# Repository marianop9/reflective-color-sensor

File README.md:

# Sensor de Colores por Reflexión

Este proyecto consiste en el diseño e implementación de un **sensor de color de bajo costo** capaz de estimar el color de una superficie y representarlo en formato RGB de 24 bits. El sistema utiliza una fotorresistencia (LDR) como transductor principal, compensando sus limitaciones mediante un proceso de caracterización empírica y un circuito de acondicionamiento activo.

## Características Principales
* **Hardware:** Basado en el microcontrolador **RP2040** (Raspberry Pi Pico).
* **Iluminantes:** LEDs RGB direccionables **WS2812**, controlados mediante el hardware PIO del RP2040 para máxima precisión.
* **Acondicionamiento:** Circuito de ganancia programable utilizando el switch bilateral **CD4066**, permitiendo medir un amplio rango de resistencias del LDR (1 k&Omega; a 1 M&Omega;) sin saturación.
* **Software:** Firmware desarrollado en C con **FreeRTOS** y **TinyUSB**. Aplicación de control en Python (CLI) para procesamiento de datos.

## Principio de Funcionamiento

El sensor opera utilizando la **reflexión secuencial**. El proceso se divide en los siguientes pasos:

1. **Aislamiento:** La carcasa diseñada bloquea la luz ambiente para evitar interferencias en la medición.
2. **Iluminación:** El dispositivo enciende secuencialmente los canales Rojo, Verde y Azul de los LEDs.
3. **Detección:** El LDR recibe la luz reflejada por la superficie. Su resistencia cambia según la intensidad recibida, y el circuito de acondicionamiento convierte este cambio en una tensión medible por el ADC.
4. **Procesamiento:** El microcontrolador envía los valores a una PC vía USB (CDC), donde se calcula el color final aplicando los parámetros de calibración.

## Caracterización y Calibración del LDR

Dado que los LDR presentan baja trazabilidad y una respuesta no lineal que varía según la longitud de onda , se implementó un procedimiento de **calibración por mínimos cuadrados**.

### El Modelo
Se modela la conductancia ($G$) del LDR en función de la intensidad de la luz ($c$) mediante la ecuación:
$$G = K_a c^{\gamma}$$
Donde $K_a$ y $\gamma$ son parámetros específicos para cada color y cada componente individual.

### Proceso de Calibración
1. Se realiza un **barrido logarítmico de intensidad** (de 0 a 255) para cada canal (R, G, B) sobre una superficie blanca de referencia.
2. Se recolectan las muestras de tensión y se ajusta automáticamente la ganancia ($R_f$) para mantener la señal en la zona lineal del ADC.
3. Mediante un script de Python, se aplica la técnica de **mínimos cuadrados** sobre los datos para hallar los coeficientes $K_a$ y $\gamma$ para cada color por separado.
4. Estos coeficientes se guardan en un archivo JSON que la aplicación CLI utiliza para convertir las mediciones posteriores en códigos de color precisos.

## Estructura del Repositorio
* `/firmware`: Código fuente en C para el RP2040 (Pico-SDK).
* `/scripts`: Contiene la Aplicación CLI en Python y varios scripts de procesamiento de datos.
* `/hardware`: Modelado de las carcasas del dispositivo para impresión 3D.
* `/circuitos`: Esquemáticos del circuito de acondicionamiento y simulaciones en LTSpice.
* `/docs`: Informes técnicos detallados del proyecto.

## Resultados

Utilizando la siguiente hoja de prueba, se tomaron medidas de las superficies de color utilizando distintas aplicaciones móviles, bajo distintas condiciones de iluminación ambiente, y se compararon con las medidas obtenidas con el dispositivo.

---

- **Autores:** Federico Beck & Mariano Perez 
- **Institución:** Universidad Tecnológica Nacional - Facultad Regional San Francisco.

Entregado como trabajo integrador de las materías Médidas Electrónicas II y Técnicas Digitales III.

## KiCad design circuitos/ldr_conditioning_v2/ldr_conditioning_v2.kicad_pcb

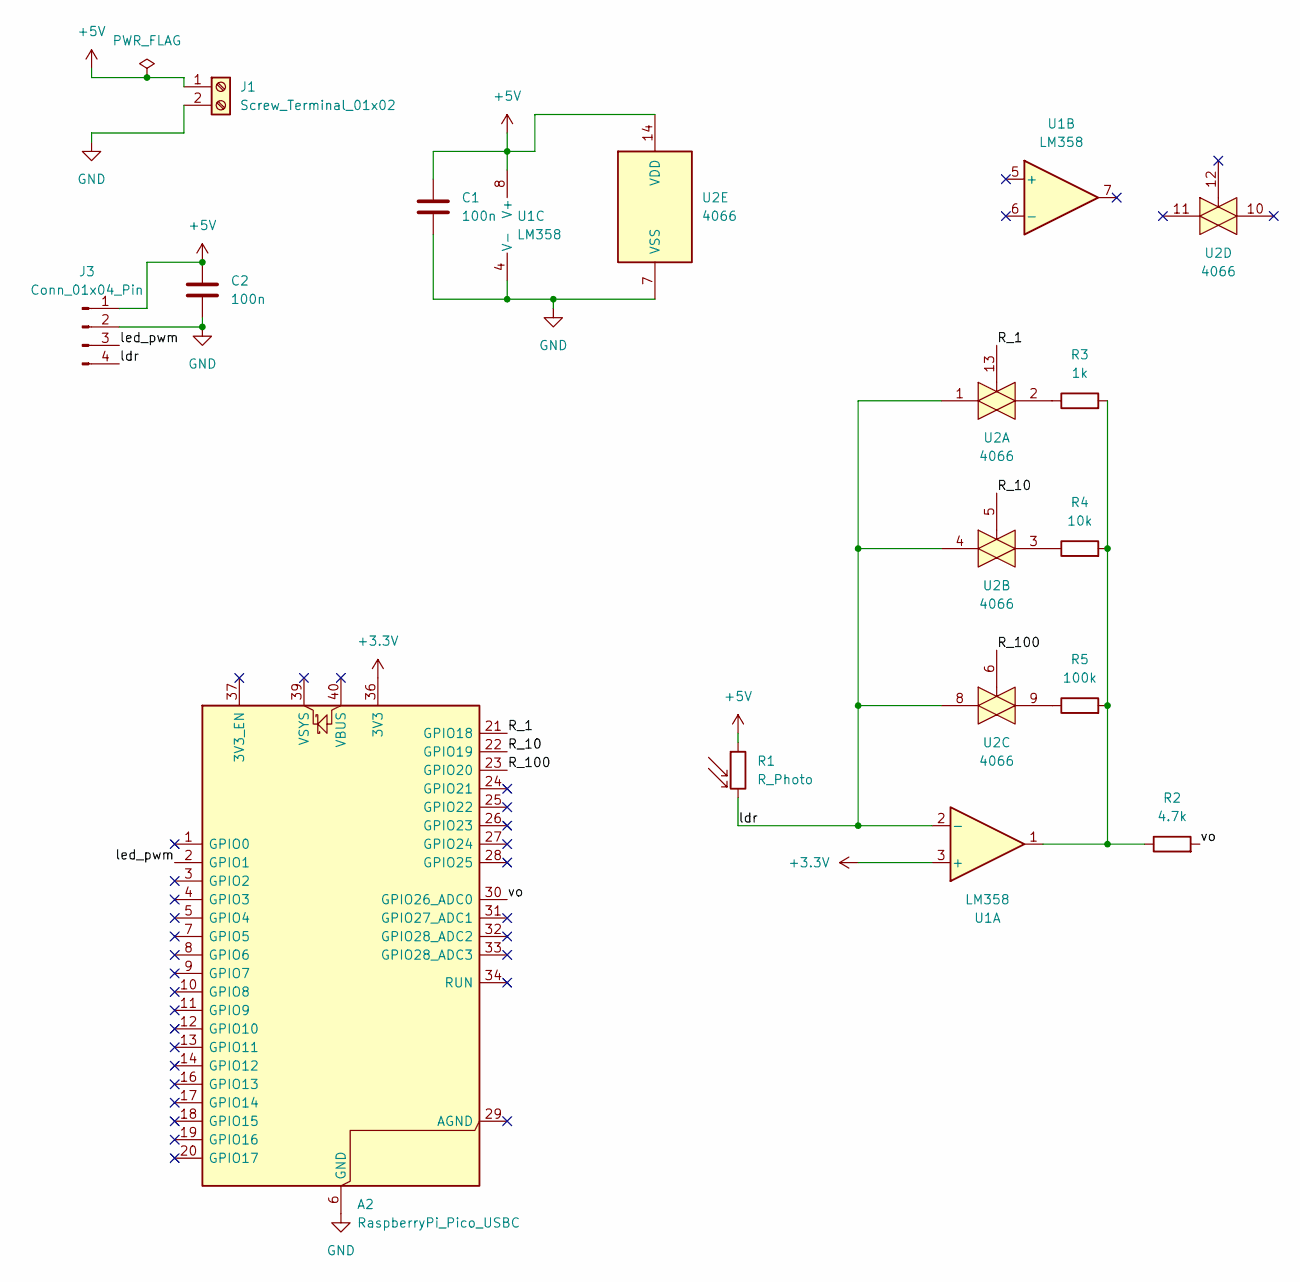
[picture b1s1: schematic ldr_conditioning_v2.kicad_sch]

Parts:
A2: RaspberryPi_Pico_USBC; RaspberryPi_Pico_Common_Unspecified
C1, C2: 100n; C_Disc_D5.0mm_W2.5mm_P2.50mm
J1: Screw_Terminal_01x02; TerminalBlock_Altech_AK300-2_P5.00mm
J3: Conn_01x04_Pin; PinHeader_1x04_P2.54mm_Vertical
R1: R_Photo; R_Axial_DIN0207_L6.3mm_D2.5mm_P10.16mm_Horizontal
R2: 4.7k; R_Axial_DIN0207_L6.3mm_D2.5mm_P10.16mm_Horizontal
R3: 1k; R_Axial_DIN0207_L6.3mm_D2.5mm_P10.16mm_Horizontal
R4: 10k; R_Axial_DIN0207_L6.3mm_D2.5mm_P10.16mm_Horizontal
R5: 100k; R_Axial_DIN0207_L6.3mm_D2.5mm_P10.16mm_Horizontal
U1: LM358; DIP-8_W7.62mm_Socket
U2: 4066; DIP-14_W7.62mm_Socket

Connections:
+3.3V: A2.36 (3V3), U1.3 (+)
+5V: C1.1, C2.1, J1.1, J3.1, R1.1, U1.8 (V+), U2.14 (VDD)
/R_1: A2.21 (GPIO18), U2.13
/R_10: A2.22 (GPIO19), U2.5
/R_100: A2.23 (GPIO20), U2.6
/ldr: J3.4, R1.2, U1.2 (-), U2.1, U2.4, U2.8
/led_pwm: A2.2 (GPIO1), J3.3
/vo: A2.30 (GPIO26_ADC0), R2.2
GND: A2.6 (GND), A2.15 (GND), A2.35 (GND), A2.38 (GND), C1.2, C2.2, J1.2, J3.2, U1.4 (V-), U2.7 (VSS)
unnamed: R2.1, R3.2, R4.2, R5.2, U1.1
unnamed: R3.1, U2.2
unnamed: R4.1, U2.3
unnamed: R5.1, U2.9

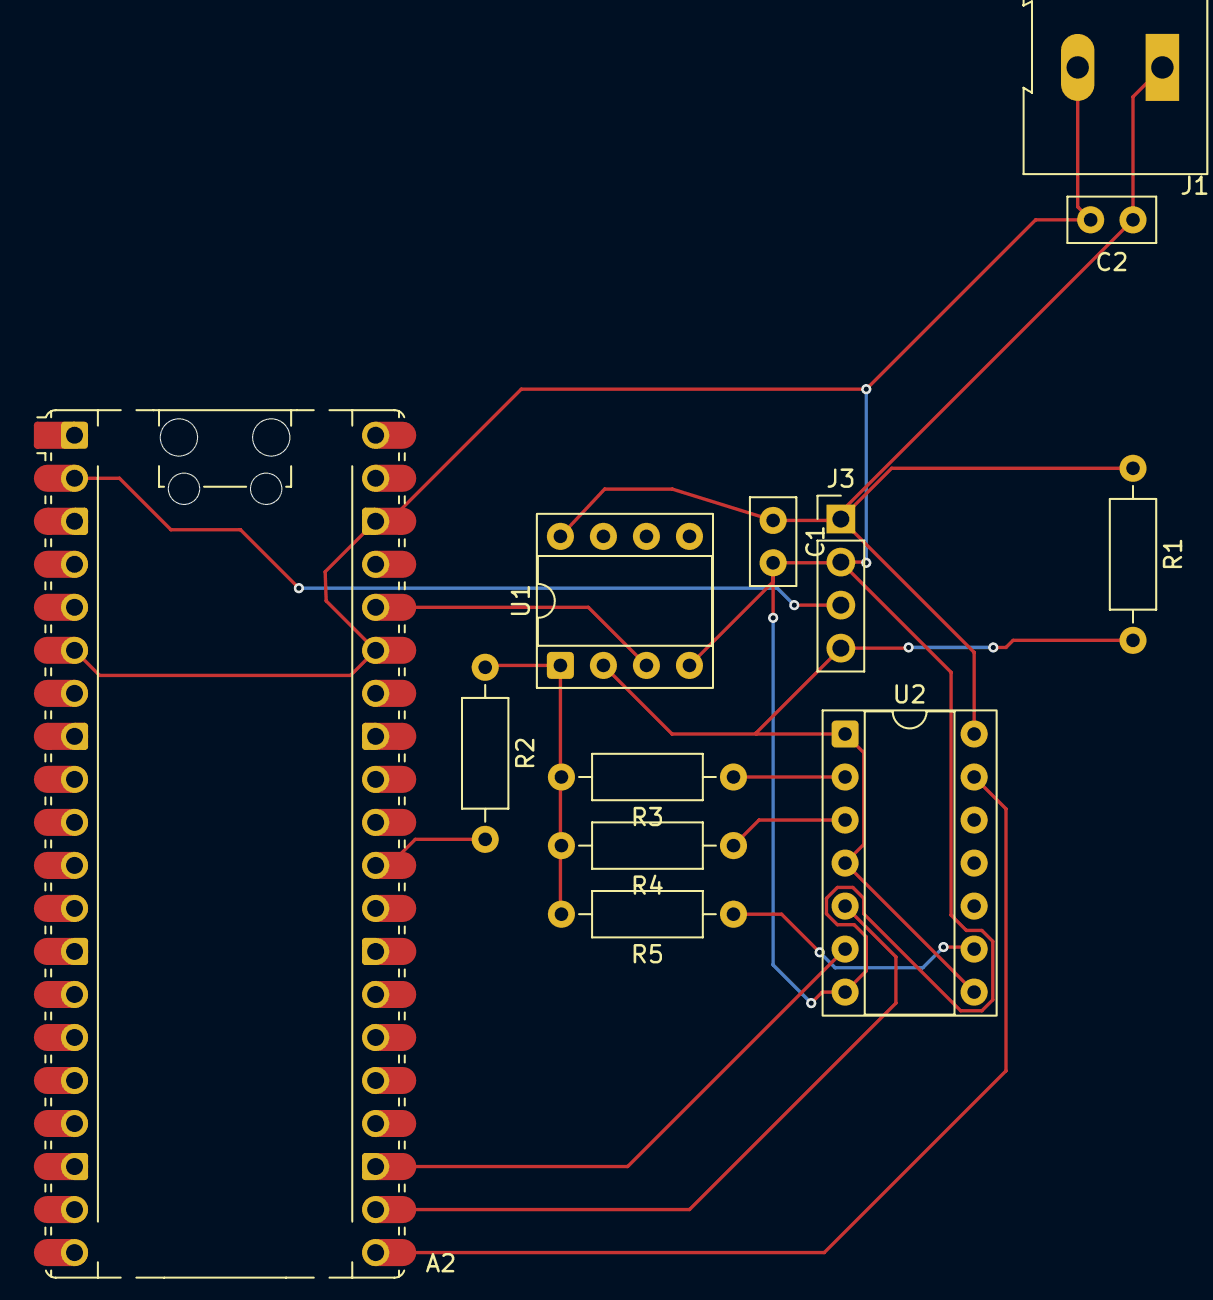
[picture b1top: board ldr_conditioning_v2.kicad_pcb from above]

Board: 2 copper layers, 12 parts (0 on the bottom side), 13 nets.

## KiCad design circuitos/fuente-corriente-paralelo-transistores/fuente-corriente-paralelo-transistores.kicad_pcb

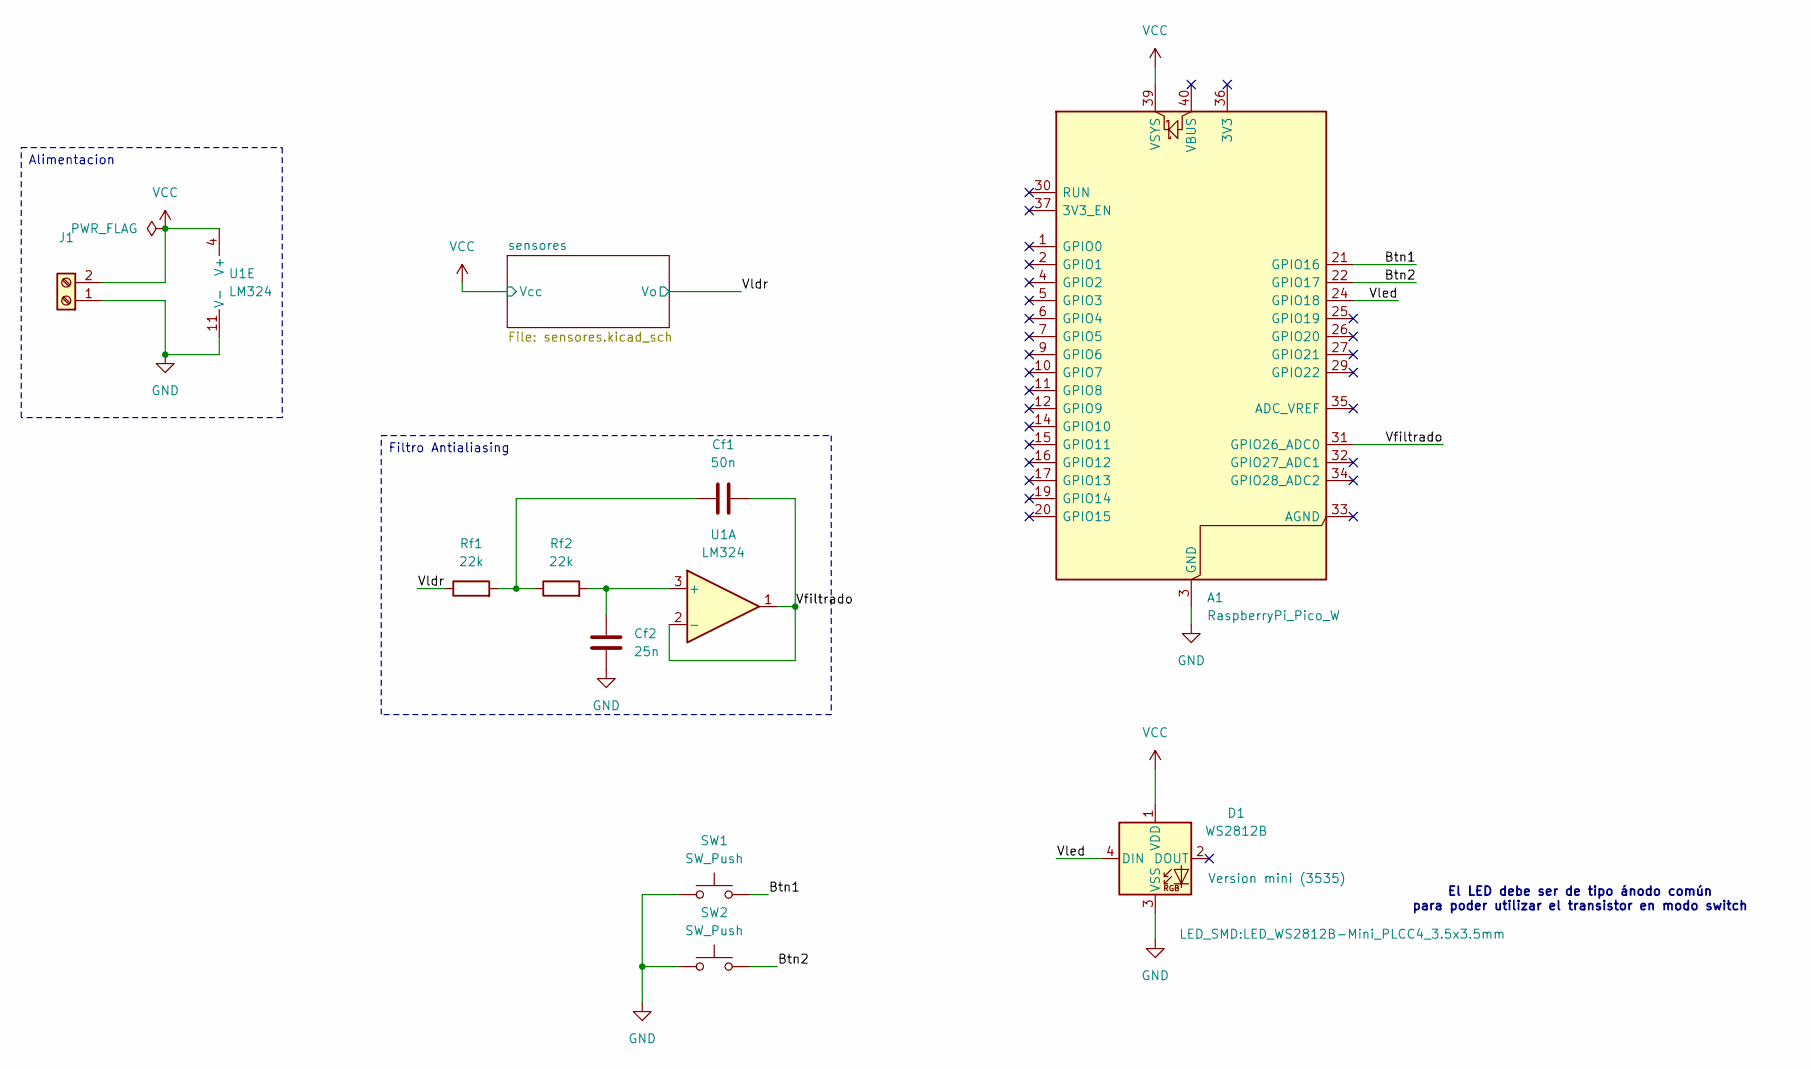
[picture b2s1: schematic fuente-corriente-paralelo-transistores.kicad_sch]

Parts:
A1: RaspberryPi_Pico_W; RaspberryPi_Pico_Common_THT
Cf1: 50n; C_Disc_D5.0mm_W2.5mm_P5.00mm
Cf2: 25n; C_Disc_D5.0mm_W2.5mm_P5.00mm
D1: WS2812B; LED_WS2812B-Mini_PLCC4_3.5x3.5mm
J1: TerminalBlock_bornier-2_P5.08mm
Rf1, Rf2: 22k; R_Axial_DIN0207_L6.3mm_D2.5mm_P7.62mm_Horizontal
SW1, SW2: SW_Push; SW_PUSH-12mm
U1: LM324; DIP-14_W7.62mm_Socket

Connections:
/Btn1: A1.21 (GPIO16), SW1.2
/Btn2: A1.22 (GPIO17), SW2.2
/Vfiltrado: A1.31 (GPIO26_ADC0), Cf1.1, U1.1, U1.2 (-)
/Vldr: Rf1.1; also elsewhere on the board
/Vled: A1.24 (GPIO18), D1.4 (DIN)
GND: A1.3 (GND), A1.8 (GND), A1.13 (GND), A1.18 (GND), A1.23 (GND), A1.28 (GND), A1.38 (GND), Cf2.2, D1.3 (VSS), J1.1, SW1.1, SW2.1, U1.11 (V-); also elsewhere on the board
unnamed: Cf1.2, Rf1.2, Rf2.1
unnamed: Cf2.1, Rf2.2, U1.3 (+)
VCC: A1.39 (VSYS), D1.1 (VDD), J1.2, U1.4 (V+); also elsewhere on the board

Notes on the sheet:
El LED debe ser de tipo ánodo común para poder utilizar el transistor en modo switch
Filtro Antialiasing
Alimentacion

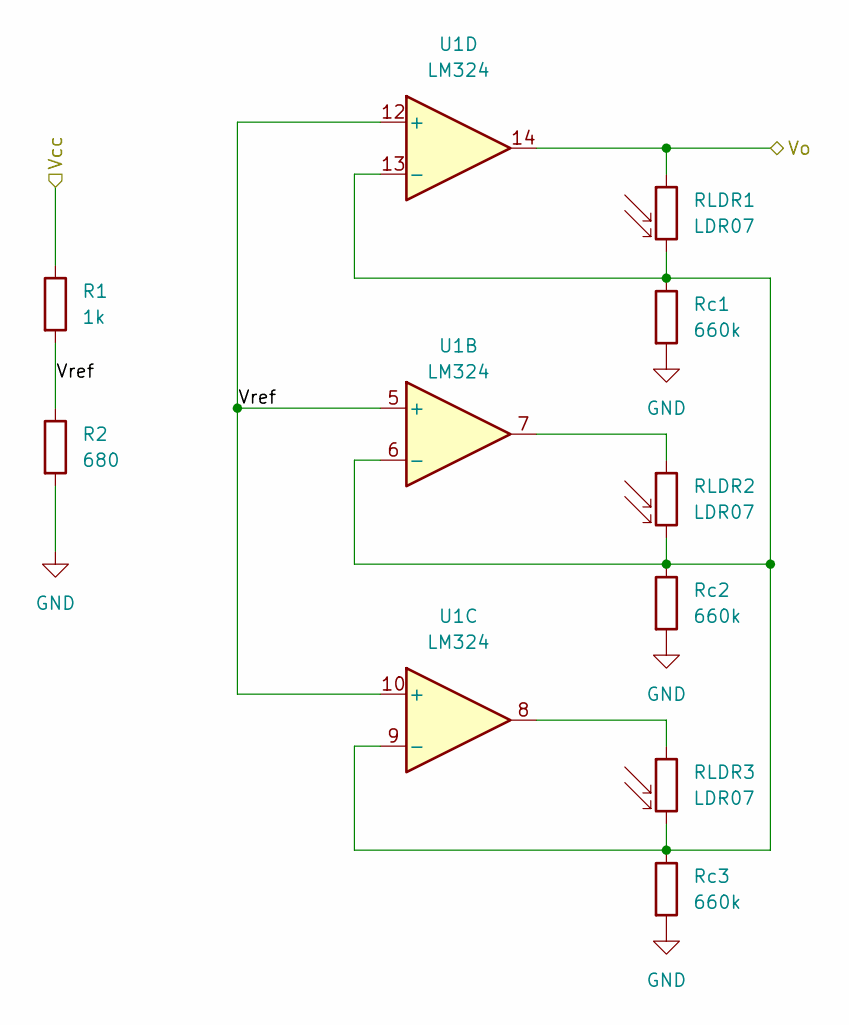
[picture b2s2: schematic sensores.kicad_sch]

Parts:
R1: 1k; R_Axial_DIN0207_L6.3mm_D2.5mm_P7.62mm_Horizontal
R2: 680; R_Axial_DIN0207_L6.3mm_D2.5mm_P7.62mm_Horizontal
RLDR1, RLDR2, RLDR3: LDR07; R_LDR_5.1x4.3mm_P3.4mm_Vertical
Rc1, Rc2, Rc3: 660k; R_Axial_DIN0207_L6.3mm_D2.5mm_P7.62mm_Horizontal
U1: LM324; DIP-14_W7.62mm_Socket

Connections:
/Vldr: RLDR1.1, U1.14; also elsewhere on the board
/sensores/Vref: R1.2, R2.1, U1.5 (+), U1.10 (+), U1.12 (+)
GND: R2.2, Rc1.2, Rc2.2, Rc3.2; also elsewhere on the board
unnamed: RLDR2.1, U1.7
unnamed: RLDR3.1, U1.8
unnamed: RLDR1.2, RLDR2.2, RLDR3.2, Rc1.1, Rc2.1, Rc3.1, U1.6 (-), U1.9 (-), U1.13 (-)
VCC: R1.1; also elsewhere on the board

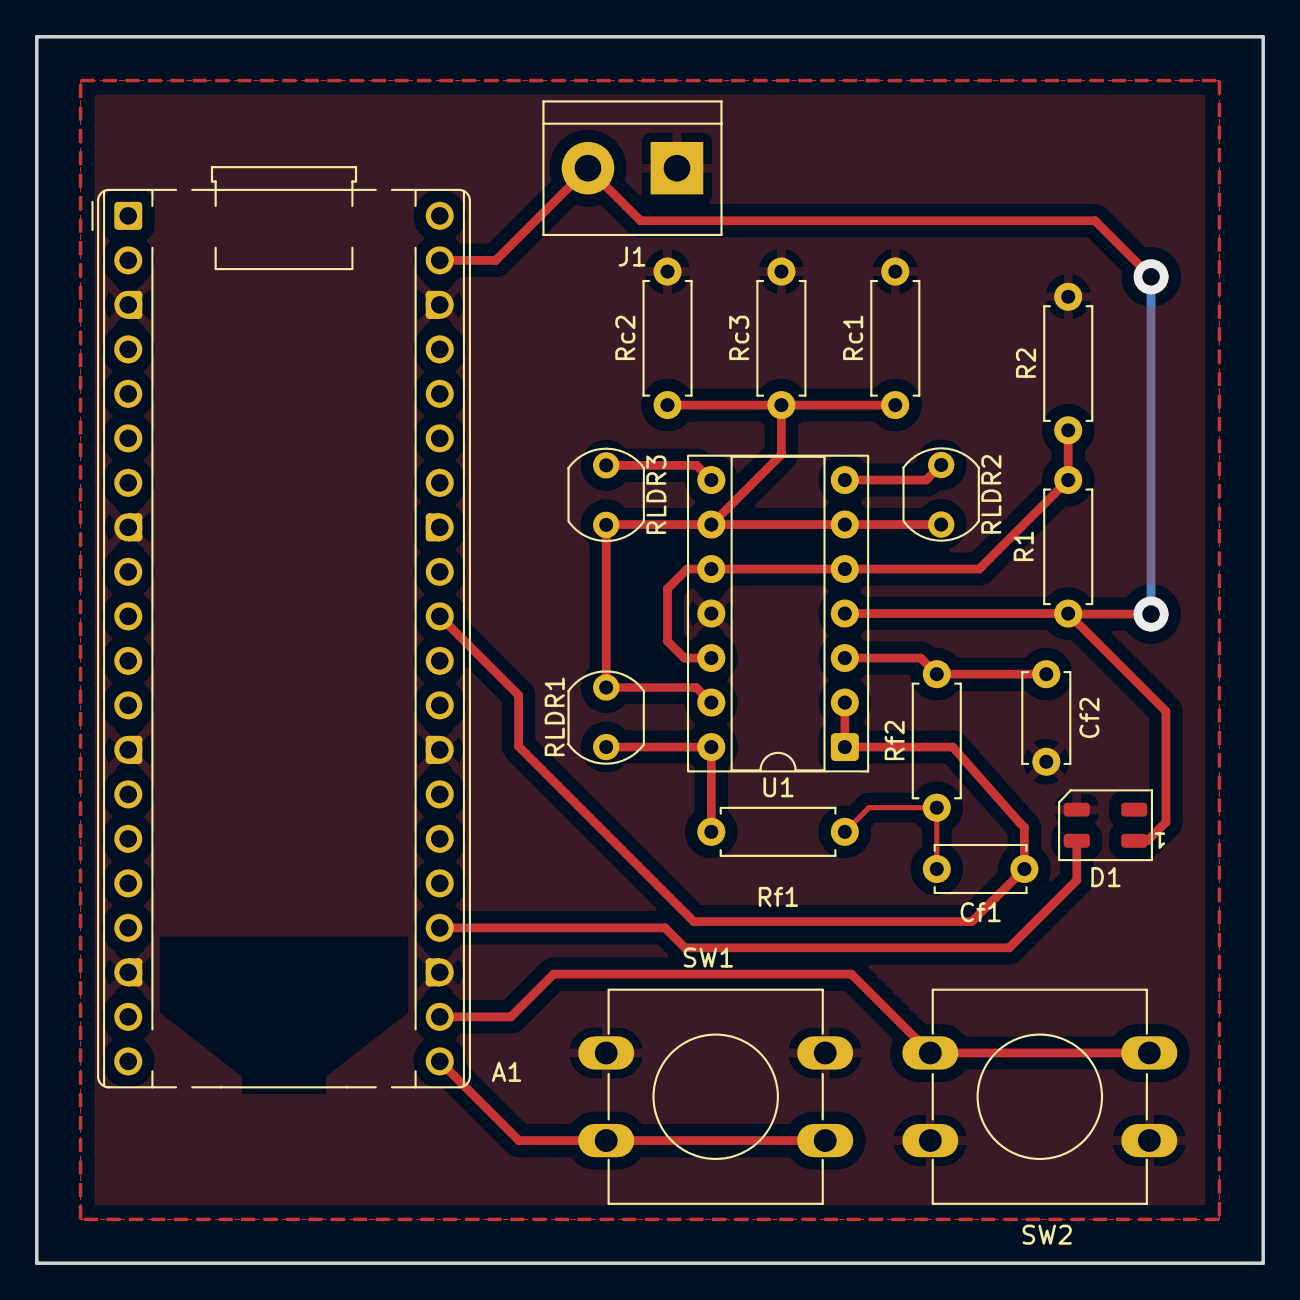
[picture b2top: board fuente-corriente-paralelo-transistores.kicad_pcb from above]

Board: 2 copper layers, 70.0 x 70.0 mm, 18 parts (0 on the bottom side), 13 nets.

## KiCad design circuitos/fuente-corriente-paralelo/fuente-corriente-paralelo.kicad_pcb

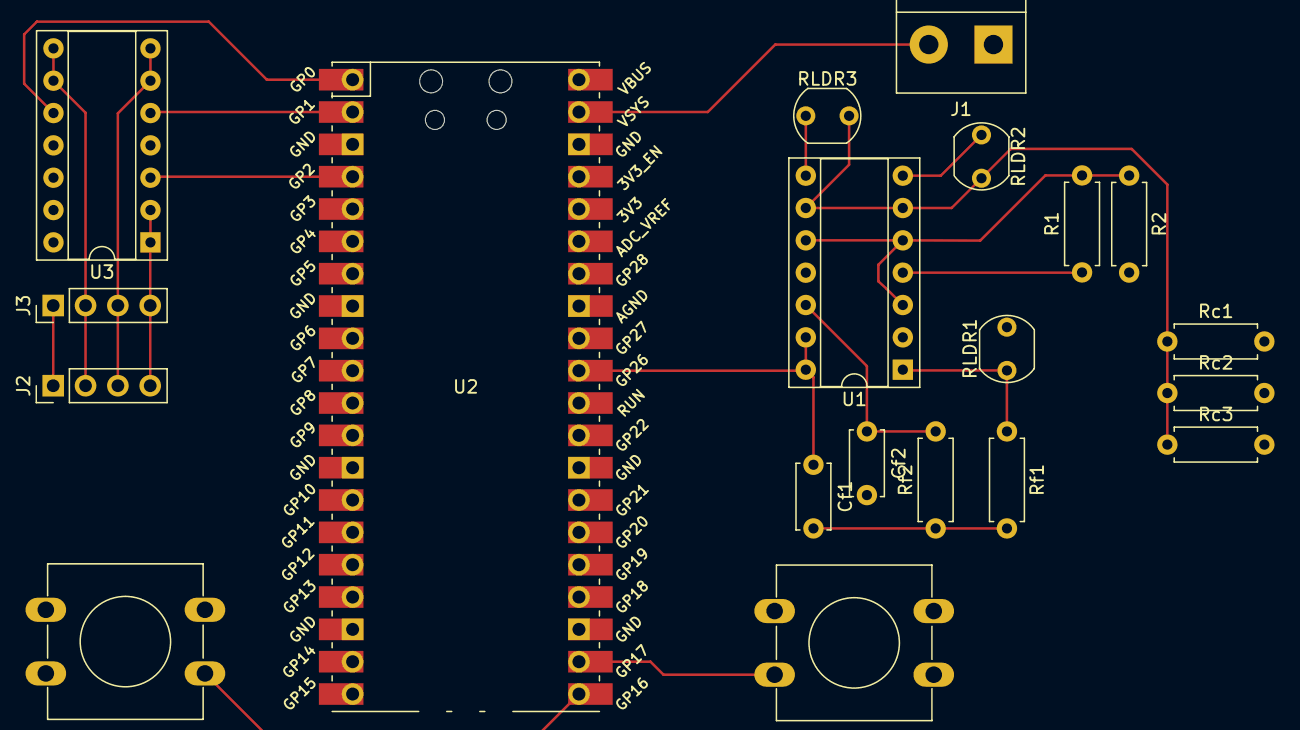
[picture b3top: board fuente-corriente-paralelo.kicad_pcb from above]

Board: 2 copper layers, 20 parts (0 on the bottom side), 18 nets.

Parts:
Cf1: 50n; C_Disc_D5.0mm_W2.5mm_P5.00mm
Cf2: 25n; C_Disc_D5.0mm_W2.5mm_P5.00mm
J1: TerminalBlock_bornier-2_P5.08mm
J2, J3: Conn_01x04_Pin; PinHeader_1x04_P2.54mm_Vertical
R1: 1k; R_Axial_DIN0207_L6.3mm_D2.5mm_P7.62mm_Horizontal
R2: 680; R_Axial_DIN0207_L6.3mm_D2.5mm_P7.62mm_Horizontal
RLDR1, RLDR2, RLDR3: LDR07; R_LDR_5.1x4.3mm_P3.4mm_Vertical
Rc1, Rc2, Rc3: 660k; R_Axial_DIN0207_L6.3mm_D2.5mm_P7.62mm_Horizontal
Rf1, Rf2: 22k; R_Axial_DIN0207_L6.3mm_D2.5mm_P7.62mm_Horizontal
SW1, SW2: SW_PUSH-12mm
U1, U3: LM324; DIP-14_W7.62mm_Socket
U2: Pico; RPi_Pico_SMD_TH

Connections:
/Btn1: SW1.1, SW1.2 (1), U2.22 (GPIO17)
/Btn2: SW2.1, SW2.2 (1), U2.21 (GPIO16)
/Vfiltrado: Cf1.1, U1.13 (-), U1.14, U2.31 (GPIO26_ADC0)
/Vldr: RLDR1.1, Rf1.1, U1.1
/VledB: U2.4 (GPIO2), U3.3 (+)
/VledG: U2.2 (GPIO1), U3.5 (+)
/VledR: U2.1 (GPIO0), U3.10 (+)
/sensores/Vref: R1.2, R2.1, U1.3 (+), U1.5 (+), U1.10 (+)
GND: Cf2.2, J1.1, J2.1, J3.1, R2.2, Rc1.2, Rc2.2, Rc3.2, SW1.3 (2), SW1.4 (2), SW2.3 (2), SW2.4 (2), U1.11 (V-), U2.38 (GND), U3.11 (V-)
unnamed: Cf1.2, Rf1.2, Rf2.1
unnamed: J2.2, J3.2, U3.8, U3.9 (-)
unnamed: J2.3, J3.3, U3.6 (-), U3.7
unnamed: J2.4, J3.4, U3.1, U3.2 (-)
unnamed: RLDR2.1, U1.7
unnamed: RLDR3.1, U1.8
unnamed: RLDR1.2, RLDR2.2, RLDR3.2, Rc1.1, Rc2.1, Rc3.1, U1.2 (-), U1.6 (-), U1.9 (-)
unnamed: Cf2.1, Rf2.2, U1.12 (+)
VCC: J1.2, R1.1, U1.4 (V+), U2.39 (VSYS), U3.4 (V+)

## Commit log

2024-10-16 init repo, add pico-sdk submodulo
2024-10-16 pico_w hello world
2024-10-24 pico adc test
2024-10-28 libreria lcd basica
2024-10-30 mostrar valores en lcd
2024-10-31 test pico adc+dma
2024-11-02 rbg adc + pasa-bajos
2024-11-04 web server - hola mundo
2024-11-05 contenido html dinámico con SSI
2024-11-06 aplicación ejemplo de servidor web
2024-11-06 mover server a libreria - incompleto
2024-11-06 libreria web_server
2024-11-07 iniciar medicion desde pagina web
2024-11-07 calibracion sensor
2024-11-09 agrego script para recibir datos por puerto serie y graficar
2024-11-10 se agrega el filtro digital
2024-11-10 guardar mediciones previas en pagina web
2024-11-12 programa de calibracion
    lee y filtra los valores muestreados por el ADC y los imprime directamente, sin la conversion a hex RGB.
    Se utilizó para determinar los valores de calibración para superficies negras y blancas. Entre estos dos puntos se linealizan las medidas del sensor.
2024-11-12 se ajustan los valores de calibración. Entrega mediciones aceptables
2024-11-17 titulo de la pagina web
2024-11-17 agrego informe
2025-02-21 reestructuracion del repo
2025-03-05 agrego posibles circuitos
2025-03-07 kicad update v9.0
2025-03-08 :memo: README
2025-04-26 pcb con LDRs y led ws2812b-mini
2025-04-26 rename source code folder
2025-04-26 agrego pico-sdk v2.1.1
2025-05-01 actualización del README y organización de los scripts de python
2025-05-01 fix image path
2025-10-21 cambio nombre carpeta
2025-10-21 Fix image path in README.md
2025-10-21 update pico-sdk
2025-11-21 diseño de carcasa - v1
    incluyo archivos de paleta de colores p/ calibracion y diagrama
2025-11-27 serial tool
2025-11-27 muevo scripts viejos
2025-11-27 rename scripts
2025-12-01 circuito acondicionamiento + hoja calibracion
2025-12-02 cambios pre-impresion
2025-12-02 fix configuracion CMake
    - permite configurar el proyecto sin WiFi SSID/pwd
    - si no hay SSID/pwd, el error se tira al compilar, no al correr cmake
2025-12-12 create stm32 cubemx project
2025-12-12 minimal blink
2025-12-12 cubemx - add usb support
2025-12-12 minimal usb example - serial port mirror
2025-12-14 libreria comunicacion usb + tests
    Libreria p/ comunicación simple via CDC.
    Agrego target de CMake para correr los tests en PC.
2025-12-15 rename stm32 firmware folder
2025-12-16 fix usb buffer filling up
2025-12-16 add adc peripheral
2025-12-16 basic binary communication protocol + ADC
2025-12-17 serialpal - improved decoding w/ struct package
2025-12-19 basic WS2812B led controller
2025-12-19 accept command arguments via usb
2025-12-29 upper bound for cmd arguments
2025-12-29 refactor/cleanup main.c
2026-01-05 project restructre
2026-01-06 expose serialpal commands
2026-01-06 led control
2026-01-09 add Response class, fix set_led cmd
2026-01-09 serialpal CLI
2026-01-09 esquematico circuito acondicionamiento
2026-01-11 FreeRTOS configuration
2026-01-12 cambio en .gitmodules
2026-01-12 ascii communication protocol
2026-01-12 complete FreeRTOS-SMP integration
2026-01-12 readme
2026-01-12 doc - proceso de medicion
2026-01-13 comunicacion serial - mensaje de respuesta
2026-01-14 rename acp folder
2026-01-14 including Unity test framework
    succesfully failed a test!
2026-01-14 :twisted_rightwards_arrows: merge test into main
2026-01-14 acp commands and responses + tests
2026-01-16 ws2812 driver + demo
2026-01-18 update serial comm protocol
2026-01-19 Resolución de conflictos de fusión CMakelists
2026-01-19 :sparkles: ascii-comm-proto
2026-01-19 :hammer: arreglos
2026-01-19 :hammer: programa para enviar y recibir datos por puerto serie
2026-01-21 restore changes: serial comm protocol
2026-01-22 tinyusb+freertos integration
2026-01-22 parser de comandos y comunicación serial por python
2026-01-22 usb communication w/ host
2026-01-23 comando para recibir los datos del adc.
    Por alguna razon, la respuesta del ADC no se envia hasta que el host manda un segundo comando. Hay que debugear
2026-01-28 esquematico actualizado + pico usb-c sym
2026-01-29 programa de prueba p/ leds
2026-01-29 fix respuesta comando ADC
    El problema es que la tarea `usb_task()` recibe las respuestas a traves de un MessageBuffer. No se puede bloquear leyendo este MessageBuffer porque la tarea es responsable de ejecutar todo el stack U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
    Como `tud_task()` bloquea indefinidamente cuando procesa todos los eventos del stack, puede que la respuesta no se llegue a leer del MessageBuffer antes de que pasen los 3ms. Esto solo pasaba con el 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
2026-01-30 doc - debuggear con stlink
2026-01-30 cd4066 resistor picker
2026-01-31 cambios driver cd4066
2026-02-03 integro driver ws2812 + visualizacion de mediciones
2026-02-11 mover logica de decodificacion a clase Response
2026-02-16 respuesta especifica para errores
2026-02-16 barrido por canal
2026-02-16 prueba caracterizacion canal R
2026-02-17 caracterizacion RGB
2026-02-18 prueba medicion: mide mal
2026-02-18 mediciones empiezan con Rf grande
    - mejoraron las medicinoes
2026-02-18 grafico respuesta LDR
2026-02-19 informe desde entrega de avance
2026-02-21 avance informe 21/2 - descripción general - circuito
2026-02-26 proceso calibracion
2026-02-27 resultados medicion
2026-03-04 avance informe 4/3 - impl. software
2026-03-04 mejorar graficos p/ informe
2026-03-06 avance informe 5/3 - impl. software
2026-04-01 informe-2025 linea de comandos
2026-04-01 informe controlado
2026-04-02 diagramas
2026-04-02 formato informe - presentacion beamer
2026-04-02 informe completo
2026-04-04 resumen p/ informe - presentacion completa
2026-04-08 presentacion - ajustes finales
2026-04-09 estructurar repo y nuevo README
